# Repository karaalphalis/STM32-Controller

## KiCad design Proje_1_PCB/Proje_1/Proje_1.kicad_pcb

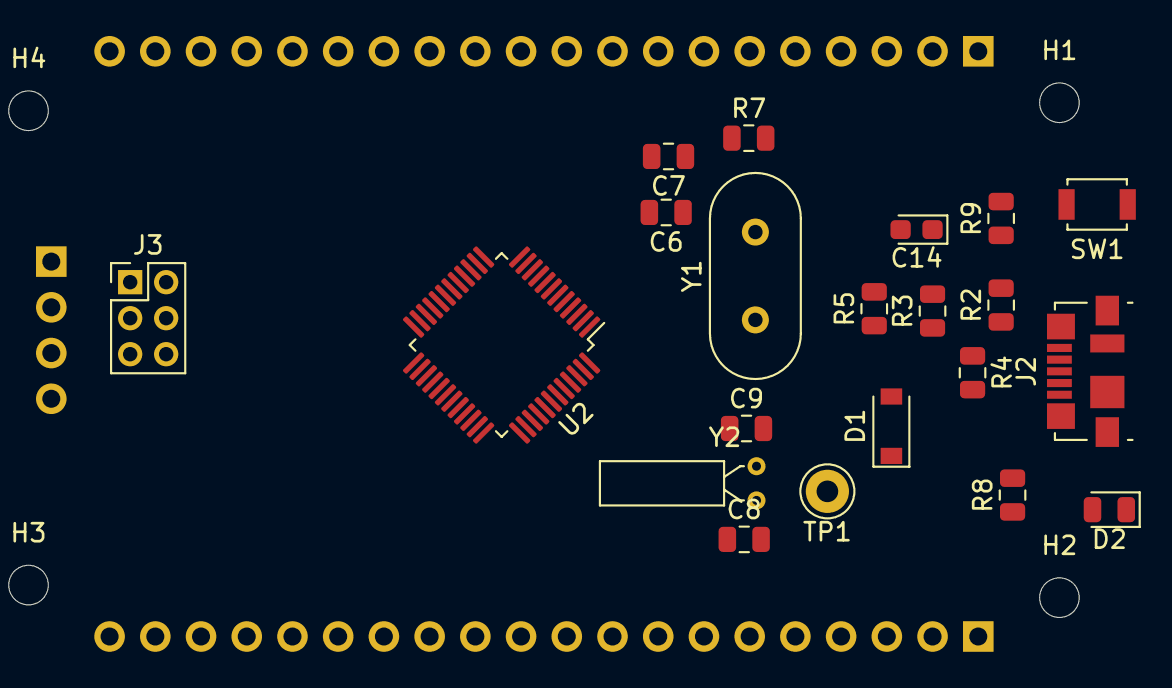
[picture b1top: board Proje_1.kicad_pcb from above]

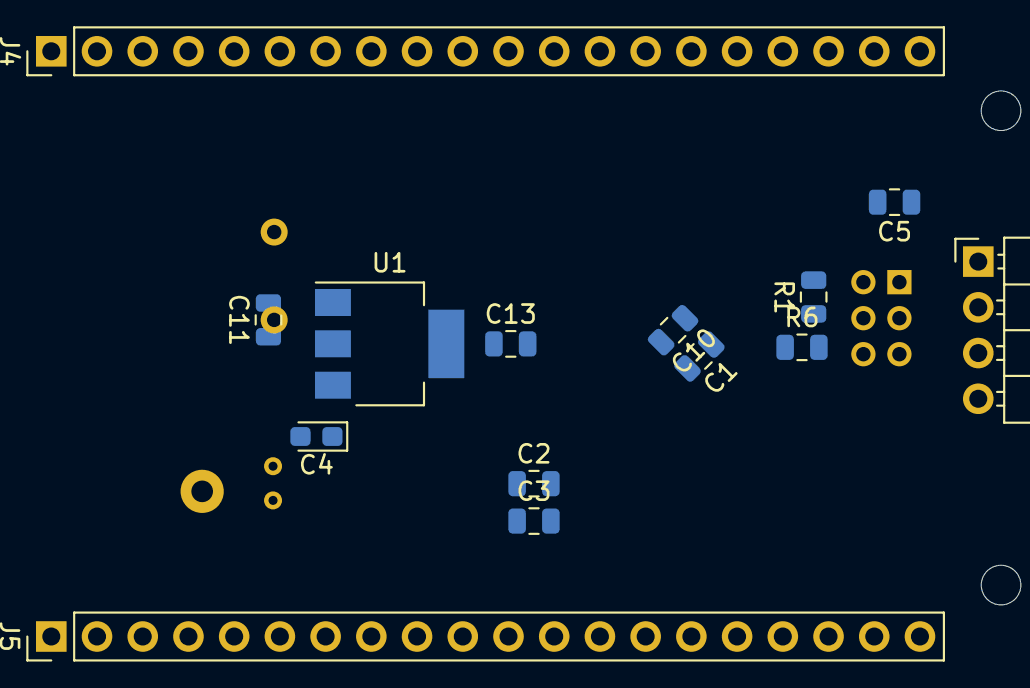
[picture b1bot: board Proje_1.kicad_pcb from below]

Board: 2 copper layers, 39 parts (14 on the bottom side), 50 nets, no tracks yet.

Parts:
C1, C2, C3, C5, C10, C13: 100nF; C_0805_2012Metric
C4: 10uF; CP_EIA-2012-15_AVX-P
C6, C7: 20pF; C_0805_2012Metric
C8, C9: 6.8pF; C_0805_2012Metric
C11: 10uF; C_0805_2012Metric
C14: 1uF; CP_EIA-2012-15_AVX-P
D1: D_Schottky; D_SOD-123
D2: LED; LED_0805_2012Metric
H1, H2, H3, H4: MountingHole; MountingHole_2.2mm_M2_DIN965
J1: SWD_CONNECTOR; PinHeader_1x04_P2.54mm_Horizontal
J2: USB_B_Micro; USB_Micro-B_Molex_47346-0001
J3: BOOTX; PinHeader_2x03_P2.00mm_Vertical
J4: I/O_HEADER1; PinHeader_1x20_P2.54mm_Vertical
J5: I/O_HEADER2; PinHeader_1x20_P2.54mm_Vertical
R1, R6: 10K; R_0805_2012Metric
R2: 100K; R_0805_2012Metric
R3, R4: 20R; R_0805_2012Metric
R5, R9: 1K5; R_0805_2012Metric
R7: 1M; R_0805_2012Metric
R8: 1K; R_0805_2012Metric
SW1: RESET_BUTTON; SW_SPST_B3U-1000P
TP1: TestPoint; Pin_D1.0mm_L10.0mm_LooseFit
U1: LD1117S33TR_SOT223; SOT-223-3_TabPin2
U2: STM32F103C8Tx; LQFP-48_7x7mm_P0.5mm
Y1: 8MHz; Crystal_HC49-4H_Vertical
Y2: 32.768KHz; Crystal_C26-LF_D2.1mm_L6.5mm_Horizontal

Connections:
3V3: C1.1, C2.1, C3.1, C5.1, C10.1, C11.1, C13.1, J1.1, J3.1, J3.2, J4.18, J5.1, R5.1, R8.2, R9.1, TP1.1, U1.2, U2.9, U2.24, U2.36, U2.48
BOOT0: R1.2, U2.44
BOOT1-PB2: R6.1, U2.20
GND: C1.2, C2.2, C3.2, C4.2, C5.2, C6.1, C7.1, C8.1, C9.1, C10.2, C11.2, C13.2, C14.2, D2.1, J1.4, J2.5, J2.6, J3.5, J3.6, J4.19, J4.20, J5.2, R2.2, SW1.1, U1.1, U2.8, U2.23, U2.35, U2.47
unnamed: D1.2, J2.1
unnamed: D2.2, R8.1
unnamed: J2.2, R4.2
unnamed: J2.3, R3.1
unnamed: J2.4, R2.1
unnamed: J3.3, R1.1
unnamed: J3.4, R6.2
OSCIN-PD0: C6.2, R7.1, U2.5, Y1.2
OSCOUT-PD1: C7.2, R7.2, U2.6, Y1.1
PA0: J4.5, U2.10
PA1: J4.6, U2.11
PA2: J4.7, U2.12
PA3: J4.8, U2.13
PA4: J4.9, U2.14
PA5: J4.10, U2.15
PA6: J4.11, U2.16
PA7: J4.12, U2.17
PA8: J5.16, U2.29
PA9: J5.15, U2.30
PA10: J5.14, U2.31
PA11: J5.13, R4.1, U2.32
PA12: J5.12, R3.2, R5.2, U2.33
PA15: J5.11, U2.38
PB0: J4.13, U2.18
PB1: J4.14, U2.19
PB3: J5.10, U2.39
PB4: J5.9, U2.40
PB5: J5.8, U2.41
PB6: J5.7, U2.42
PB7: J5.6, U2.43
PB8: J5.5, U2.45
PB9: J5.4, U2.46
PB10: J4.15, U2.21
PB11: J4.16, U2.22
PB12: J5.20, U2.25
PB13: J5.19, U2.26
PB14: J5.18, U2.27
PB15: J5.17, U2.28
PC13: J4.2, U2.2
PC14: C8.2, J4.3, U2.3, Y2.2
PC15: C9.2, J4.4, U2.4, Y2.1
RESET: C14.1, J4.17, R9.2, SW1.2, U2.7
SWDCLK-PA14: J1.3, U2.37
SWDIO-PA13: J1.2, U2.34
USB_5V: C4.1, D1.1, J5.3, U1.3
VBAT: J4.1, U2.1

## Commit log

2025-03-06 Proje Yüklendi
